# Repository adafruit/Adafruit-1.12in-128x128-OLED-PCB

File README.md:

## Adafruit Monochrome 1.12in 128x128 OLED Graphic Display PCB

<a href="http://www.adafruit.com/products/5297"><br/>
Click here to purchase one from the Adafruit shop</a>

PCB files for the Adafruit Monochrome 1.12in 128x128 OLED Graphic Display. 

Format is EagleCAD schematic and board layout
* https://www.adafruit.com/product/5297

### Description

This OLED goes out to all the fans who want more pixels in a smaller size! Normally our 128x64 OLEDs are the biggest ones we've stocked that can use I2C. This one is a whopping 128x128 pixels in crisp monochrome.

This display is a petite 1.12" diagonal, but very readable due to the high contrast of an OLED display. This display is made of 128x128 individual white OLED pixels, each one is turned on or off by the controller chip. Because the display makes its own light, no backlight is required. This reduces the power required to run the OLED and is why the display has such high contrast; we really like these miniature displays for their crispness!

The driver chip, SSD1107 can communicate in two ways: I2C or SPI. The OLED itself requires a 3.3V and 12V power supply and 3.3V logic levels for communication. We include a 3.3V regulator and 12V boost converter, and all pins are fully level shifted so you can use with 3V or 5V devices!

If you are using I2C, we've included SparkFun qwiic compatible STEMMA QT connectors for the I2C bus so you don't even need to solder! Plug and play with any board that has a Qwiic or STEMMA QT connector for effortless prototyping and development. QT Cable is not included, but we have a variety in the shop.

This display, being 128x128 pixels, requires 128 * 128 = 2KB of SRAM just to buffer the display. So you can't use it with a small chip such as the Arduino UNO (ATmega328 or 32u4). Pick a microcontroller or microcomputer with 16KB+ RAM - a SAMD21, SAMD51, ESP, nRF52, Teensy, etc will do an excellent job. As long as you have I2C or SPI interface available, you're good to go - SPI will be much faster but I2C requires fewer pins.

We have both Arduino and CircuitPython support for this display chipset (SH1107).

Please note that OLED displays are made of hundreds of...OLEDs! That means each pixel is a little organic LED, and if it's kept on for over 1000 hours it'll start to dim. If you want to keep the display uniformly bright, please turn off the display (set the pixels off) when it isn't needed to keep them from dimming.

### License

Adafruit invests time and resources providing this open source design, please support Adafruit and open-source hardware by purchasing products from [Adafruit](https://www.adafruit.com)!

Designed by Limor Fried/Ladyada for Adafruit Industries.

Creative Commons Attribution/Share-Alike, all text above must be included in any redistribution. 
See license.txt for additional details.

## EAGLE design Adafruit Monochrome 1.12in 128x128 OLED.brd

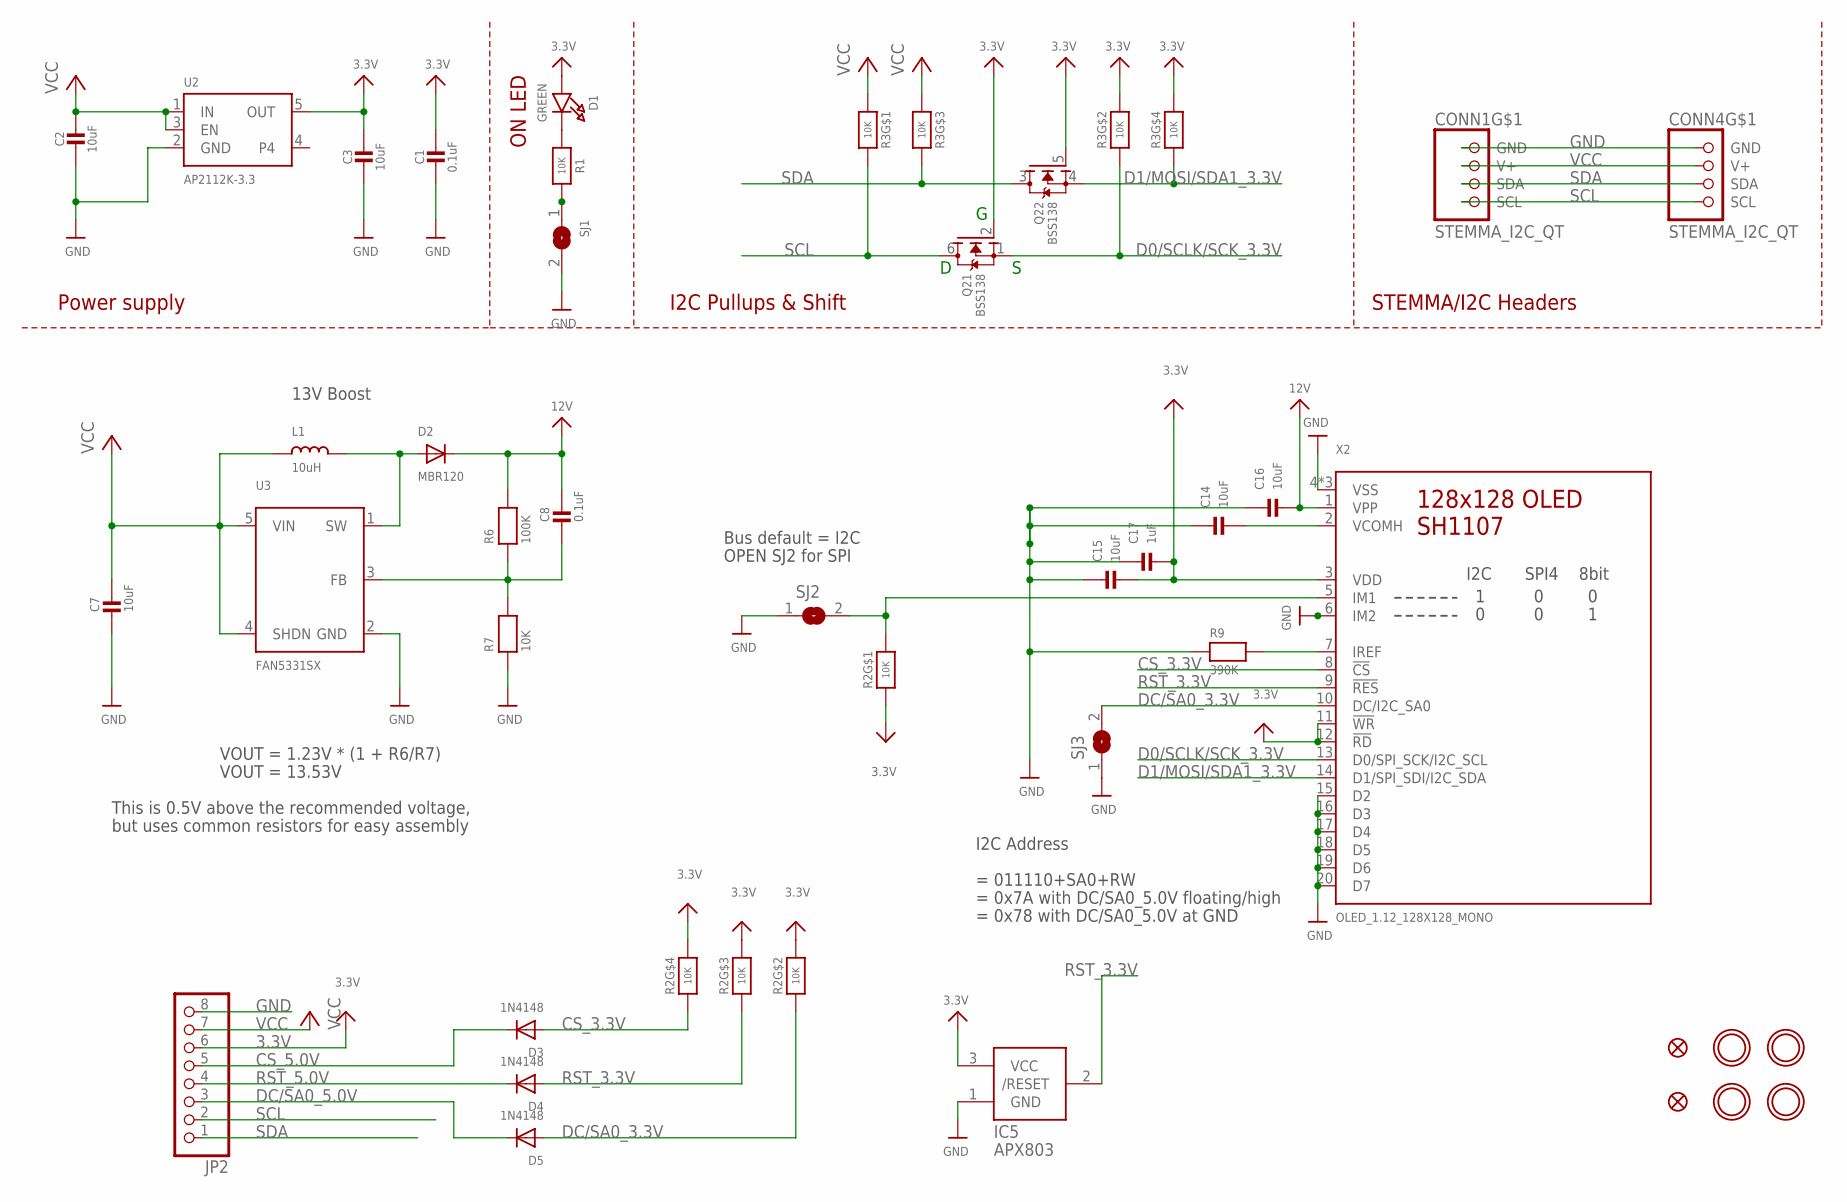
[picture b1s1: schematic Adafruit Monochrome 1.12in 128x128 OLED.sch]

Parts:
C1, C8: 0.1uF; 0603-NO
C2, C3, C7, C14, C15, C16: 10uF; 0805-NO
C17: 1uF; 0603-NO
CONN1, CONN4: STEMMA_I2C_QT; JST_SH4
D1: GREEN; CHIPLED_0603_NOOUTLINE
D2: MBR120; SOD-123
D3, D4, D5: 1N4148; SOD-323
FID3, FID4: FIDUCIAL_1MM
IC5: APX803; SOT23
JP2: HEADER-1X876MIL; 1X08_ROUND_76
L1: 10uH; INDUCTOR_1007
Q2: BSS138; SOT363
R1, R7: 10K; 0603-NO
R2, R3: 10K; RESPACK_4X0603
R6: 100K; 0603-NO
R9: 390K; 0603-NO
SJ1: SOLDERJUMPERCLOSED; SOLDERJUMPER_CLOSEDWIRE
SJ2, SJ3: SOLDERJUMPER; SOLDERJUMPER_ARROW_NOPASTE
U2: AP2112K-3.3; SOT23-5
U3: FAN5331SX; SOT23-5@1
U$1, U$17, U$19, U$21: MOUNTINGHOLE3.0THIN; MOUNTINGHOLE_3.0_PLATEDTHIN
X2: OLED_1.12_128X128_MONO; OLED_1.12IN_128X128MONO

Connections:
3.3V: C1.1, C3.1, C15.2, C17.2, D1.A, IC5.3 (VCC), JP2.6, Q2.2 (G), Q2.5 (G), R2.1, R2.5 (2), R2.6 (2), R2.7 (2), R3.2 (1), R3.4 (1), U2.5 (OUT), X2.3 (VDD), X2.11 (!WR), X2.12 (!RD)
12V: C8.1, C16.2, D2.C, R6.2, X2.1 (VPP)
CS_3.3V: D3.A, R2.4 (1), X2.8 (!CS)
CS_5.0V: D3.C, JP2.5
D0/SCLK/SCK_3.3V: Q2.1 (S), R3.7 (2), X2.13 (D0/SPI_SCK/I2C_SCL)
D1/MOSI/SDA1_3.3V: Q2.4 (S), R3.5 (2), X2.14 (D1/SPI_SDI/I2C_SDA)
DC/SA0_3.3V: D5.A, R2.2 (1), SJ3.2, X2.10 (DC/I2C_SA0)
DC/SA0_5.0V: D5.C, JP2.3
GND: C1.2, C2.2, C3.2, C7.2, C14.1, C15.1, C16.1, C17.1, CONN1.1 (GND), CONN4.1 (GND), IC5.1 (GND), JP2.8, R7.1, R9.1, SJ1.2, SJ2.1, SJ3.1, U2.2 (GND), U3.2 (GND), X2.4 (VSS), X2.6 (IM2), X2.15 (D2), X2.16 (D3), X2.17 (D4), X2.18 (D5), X2.19 (D6), X2.20 (D7), X2.21 (VSS), X2.22 (VSS)
unnamed: R1.2, SJ1.1
unnamed: D1.C, R1.1
unnamed: D2.A, L1.P$2 (2), U3.1 (SW)
unnamed: C8.2, R6.1, R7.2, U3.3 (FB)
unnamed: R2.8 (2), SJ2.2, X2.5 (IM1)
unnamed: R9.2, X2.7 (IREF)
unnamed: C14.2, X2.2 (VCOMH)
RST_3.3V: D4.A, IC5.2 (/RESET), R2.3 (1), X2.9 (!RES)
RST_5.0V: D4.C, JP2.4
SCL: CONN1.4 (SCL), CONN4.4 (SCL), JP2.2, Q2.6 (D), R3.8 (2)
SDA: CONN1.3 (SDA), CONN4.3 (SDA), JP2.1, Q2.3 (D), R3.6 (2)
VCC: C2.1, C7.1, CONN1.2 (V+), CONN4.2 (V+), JP2.7, L1.P$1 (1), R3.1, R3.3 (1), U2.1 (IN), U2.3 (EN), U3.4 (SHDN), U3.5 (VIN)

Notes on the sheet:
I2C Pullups & Shift
STEMMA/I2C Headers
ON LED
Power supply
Bus default = I2C
OPEN SJ2 for SPI
= 011110+SA0+RW
= 0x7A with DC/SA0_5.0V floating/high
= 0x78 with DC/SA0_5.0V at GND
I2C Address
VOUT = 1.23V * (1 + R6/R7)
VOUT = 13.53V
This is 0.5V above the recommended voltage,
but uses common resistors for easy assembly
13V Boost

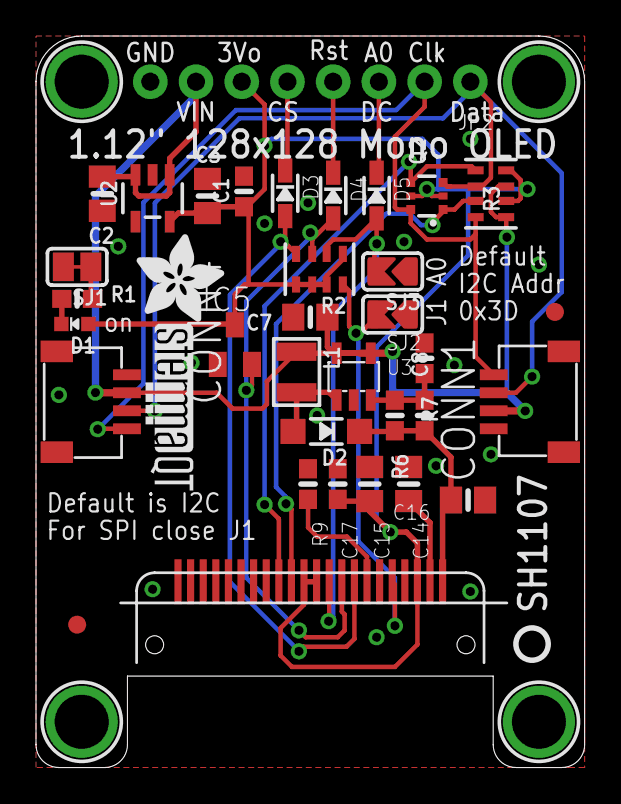
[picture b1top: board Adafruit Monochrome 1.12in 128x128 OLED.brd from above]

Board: 2 copper layers, 30.5 x 40.6 mm, 41 parts (1 on the bottom side), 21 nets.

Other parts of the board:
U$8: ADAFRUIT_5MM
U$25: PCBFEAT-REV-040
U$31: STEMMAQT

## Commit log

2021-11-09 Adding board files.

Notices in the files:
parts and their libraries:
microbuilder: This work is placed in the public domain, and may be freely used for commercial and non-commercial work with the following conditions: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
